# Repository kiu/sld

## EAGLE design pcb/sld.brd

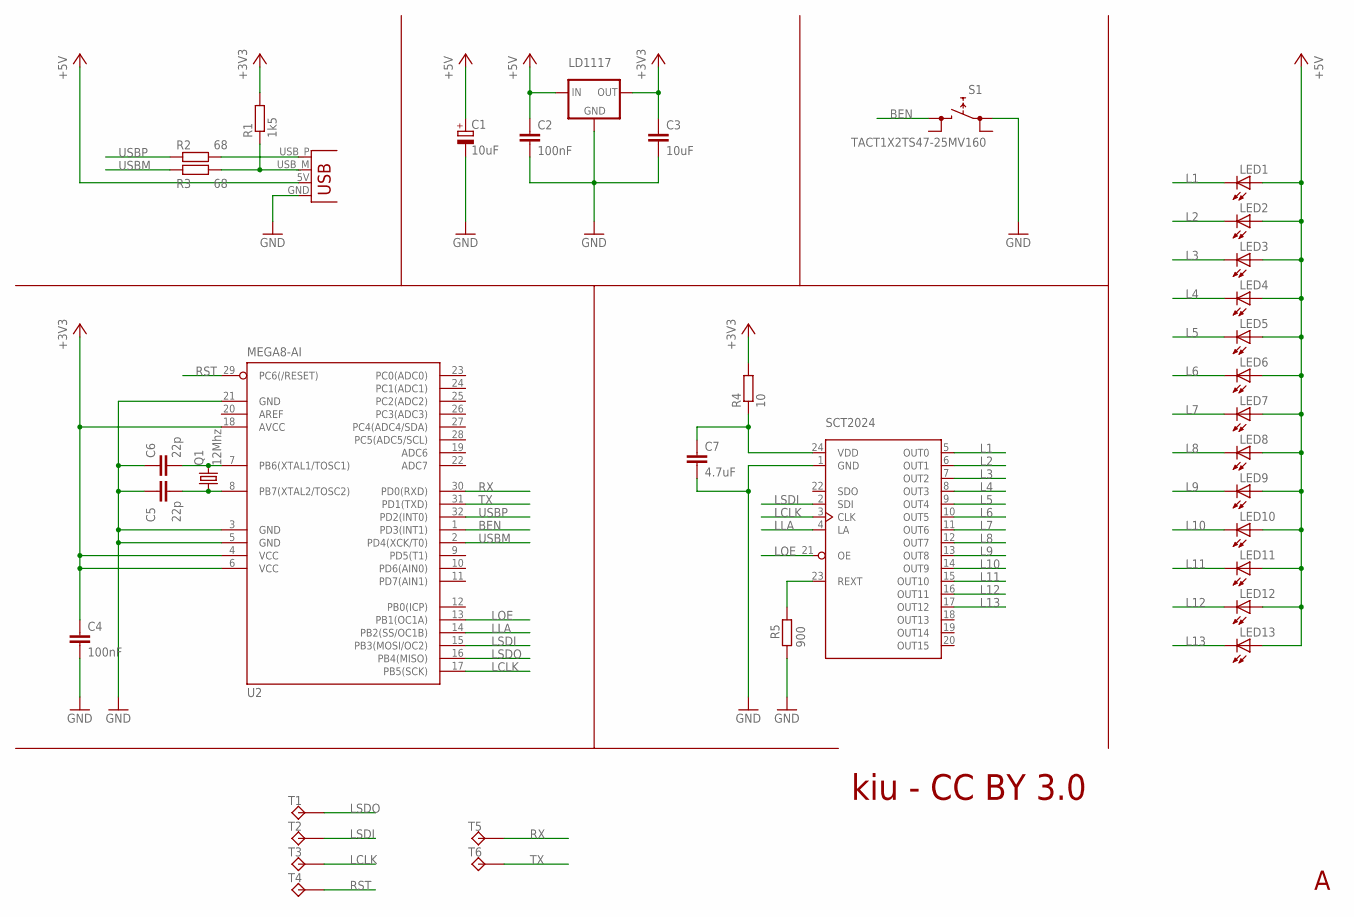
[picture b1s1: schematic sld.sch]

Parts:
C1: 10uF; CT3216
C2, C4: 100nF; C0805
C3: 10uF; C0805
C5, C6: 22p; C0805
C7: 4.7uF; C0805
JP1: USBPCB; USB-A-PCB
LED1, LED2, LED3, LED4, LED5, LED6, LED7, LED8, LED9, LED10, LED11, LED12, LED13: LEDKA-3528ASYC; KA-3528ASYC
Q1: 12Mhz; HC49UP
R1: 1k5; R0805
R2, R3: 68; R0805
R4: 10; R0805
R5: 900; R0805
S1: TACT1X2TS47-25MV160; TACT1.7X5.15
T1, T2, T3, T4, T5, T6: PAD; PAD-1X1
U1: LD1117; SOT223
U2: MEGA8-AI; TQFP32-08
U3: SCT2024; SSOP24

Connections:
+3V3: C3.1, C4.1, R1.2, R4.2, U1.2 (OUT), U2.4 (VCC), U2.6 (VCC), U2.18 (AVCC)
+5V: C1.+, C2.1, JP1.5V (VBUS), LED1.A, LED2.A, LED3.A, LED4.A, LED5.A, LED6.A, LED7.A, LED8.A, LED9.A, LED10.A, LED11.A, LED12.A, LED13.A, U1.3 (IN)
BEN: S1.2 (1), U2.1 (PD3(INT1))
GND: C1.-, C2.2, C3.2, C4.2, C5.1, C6.1, C7.2, JP1.GND, R5.2, S1.1 (0), U1.1 (GND), U2.3 (GND), U2.5 (GND), U2.21 (GND), U3.1 (GND)
L1: LED1.C, U3.5 (OUT0)
L2: LED2.C, U3.6 (OUT1)
L3: LED3.C, U3.7 (OUT2)
L4: LED4.C, U3.8 (OUT3)
L5: LED5.C, U3.9 (OUT4)
L6: LED6.C, U3.10 (OUT5)
L7: LED7.C, U3.11 (OUT6)
L8: LED8.C, U3.12 (OUT7)
L9: LED9.C, U3.13 (OUT8)
L10: LED10.C, U3.14 (OUT9)
L11: LED11.C, U3.15 (OUT10)
L12: LED12.C, U3.16 (OUT11)
L13: LED13.C, U3.17 (OUT12)
LCLK: T3.P1, U2.17 (PB5(SCK)), U3.3 (CLK)
LLA: U2.14 (PB2(SS/OC1B)), U3.4 (LA)
LOE: U2.13 (PB1(OC1A)), U3.21 (OE)
LSDI: T2.P1, U2.15 (PB3(MOSI/OC2)), U3.2 (SDI)
LSDO: T1.P1, U2.16 (PB4(MISO))
unnamed: C6.2, Q1.2, U2.7 (PB6(XTAL1/TOSC1))
unnamed: C5.2, Q1.1, U2.8 (PB7(XTAL2/TOSC2))
unnamed: R5.1, U3.23 (REXT)
unnamed: C7.1, R4.1, U3.24 (VDD)
unnamed: JP1.USB_P (D+), R2.2
unnamed: JP1.USB_M (D-), R1.1, R3.1
RST: T4.P1, U2.29 (PC6(/RESET))
RX: T5.P1, U2.30 (PD0(RXD))
TX: T6.P1, U2.31 (PD1(TXD))
USBM: R3.2, U2.2 (PD4(XCK/T0))
USBP: R2.1, U2.32 (PD2(INT0))

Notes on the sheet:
kiu - CC BY 3.0

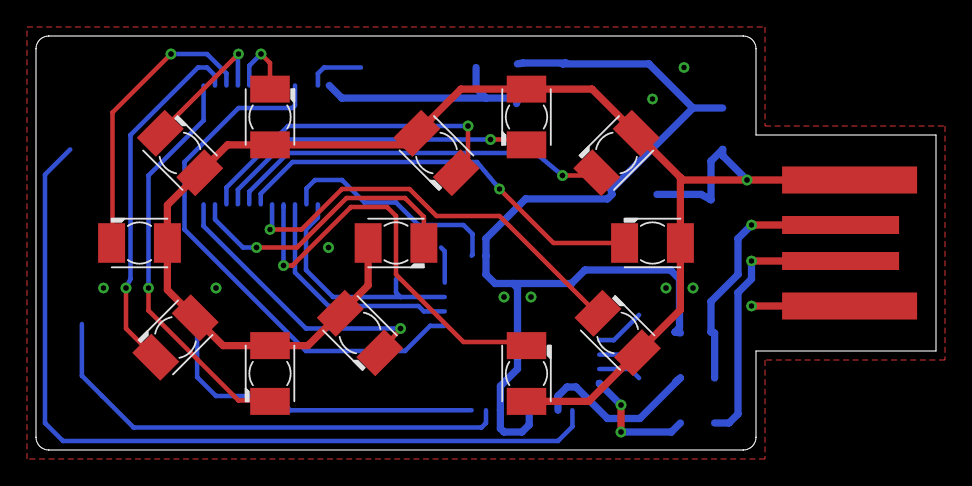
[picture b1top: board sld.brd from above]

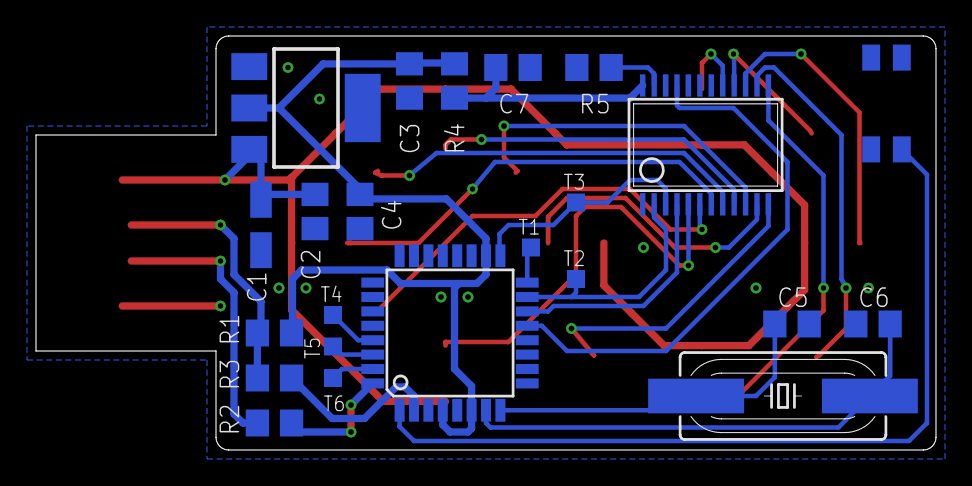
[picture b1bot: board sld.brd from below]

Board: 4 copper layers, 50.0 x 23.0 mm, 37 parts (23 on the bottom side), 33 nets.

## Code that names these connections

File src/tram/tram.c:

#include "tram.h"

#include <avr/io.h>
#include <util/delay.h>
#include <avr/interrupt.h>

volatile uint16_t leds = 0;

// Interrupt for button press
ISR (INT1_vect) {
	leds = 0;
}

void sendSPI(uint16_t data) {
	cbi(PORTB, PB2);  // Latch

	SPDR = (uint8_t) ((data & 0xFF00) >> 8);
	while (!(SPSR & (1 << SPIF)));
	SPDR; // Clear SPIF

	SPDR = (uint8_t) (data & 0x00FF);
	while (!(SPSR & (1 << SPIF)));
	SPDR; // Clear SPIF

	sbi(PORTB, PB2);  // Latch
}

void initHW() {
	// Prepare Ports
	sbi(DDRB, PB1);  // LED Output Enable Out
	sbi(DDRB, PB2);  // LED Latch Out
	sbi(DDRB, PB3);  // LED MOSI Out
	sbi(DDRB, PB5);  // LED SCK Out

	cbi(DDRD, PD3);  // Button In
	sbi(PORTD, PD3);  // Button In Pullup

	// Prepare SPI
	SPCR = (1 << MSTR) | (1 << SPE); // clk/4
	SPSR |= (1 << SPI2X);

	cbi(PORTB, PB1);  // LED Output Enable On

	EIMSK |= (1 << INT1); // Enable INT1

	// Hardware PWM reducing LED brightness
	TCCR1A = (1 << COM1A1) | (1 << WGM11) | (1 << WGM10);
	TCCR1B = (1 << CS11); // clk/8
	OCR1A = 0xFFCC;
}

int main (void) {
	initHW();

	sei(); // Enable interrupts

	// GO GO GO
	while (1) {
		sendSPI(1);
		_delay_ms(500);
	}

	return 0;
}

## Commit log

2013-12-11 Minimalist sample
2013-12-12 Extracted vanilla USBaspLoader.2012-12-08
2013-12-12 500mA power
2013-12-12 Adapted makefile to mcu, programmer, fuses, ...
2013-12-12 Adjusted bootloader configuration
2013-12-12 Stay in bootloader even though button is released
2013-12-12 readme for upstream
2013-12-12 Adjusted makefile for usbasp via bootloader 1sec blinking interval
2013-12-12 Bill Of Materials for REV A
2013-12-12 init
2013-12-12 Adding REV A board
2013-12-13 Faster startup time (fuse)
2013-12-13 Removed flashing of EEP because AVRDUDE on MAC segfaults
2013-12-13 Moved HW setup into seperate funtion
2013-12-13 Adding HW PWM for LEDs
2013-12-13 sldtool - send data from host side
2013-12-13 default firmware running on sld
2013-12-13 helper tools for mass flashing
2013-12-13 Added cpu load for MAC
2013-12-14 cleaned up cpu_mac.c. added binaries for mac.
2013-12-17 added custom poject skeleton
2013-12-17 do the hard stuff in ruby
2013-12-17 renamed to tram-countdown
2013-12-17 check for leaving tram every 10sec
2013-12-17 removed .dep dir
2013-12-17 moved to src/contrib
2013-12-17 fixed path
2013-12-17 added README
2013-12-17 if 0 minutes, show next one
2013-12-17 a little less brightness
2013-12-17 make it work with ruby 1.9 as well
2013-12-17 run with system ruby
2013-12-23 added contrib
2013-12-29 modified url
2014-03-17 allow multiple destinations

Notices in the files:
parts and their libraries:
SparkFun-Connectors: Licensing: CC v3.0 Share-Alike You are welcome to use this library for commercial purposes.
